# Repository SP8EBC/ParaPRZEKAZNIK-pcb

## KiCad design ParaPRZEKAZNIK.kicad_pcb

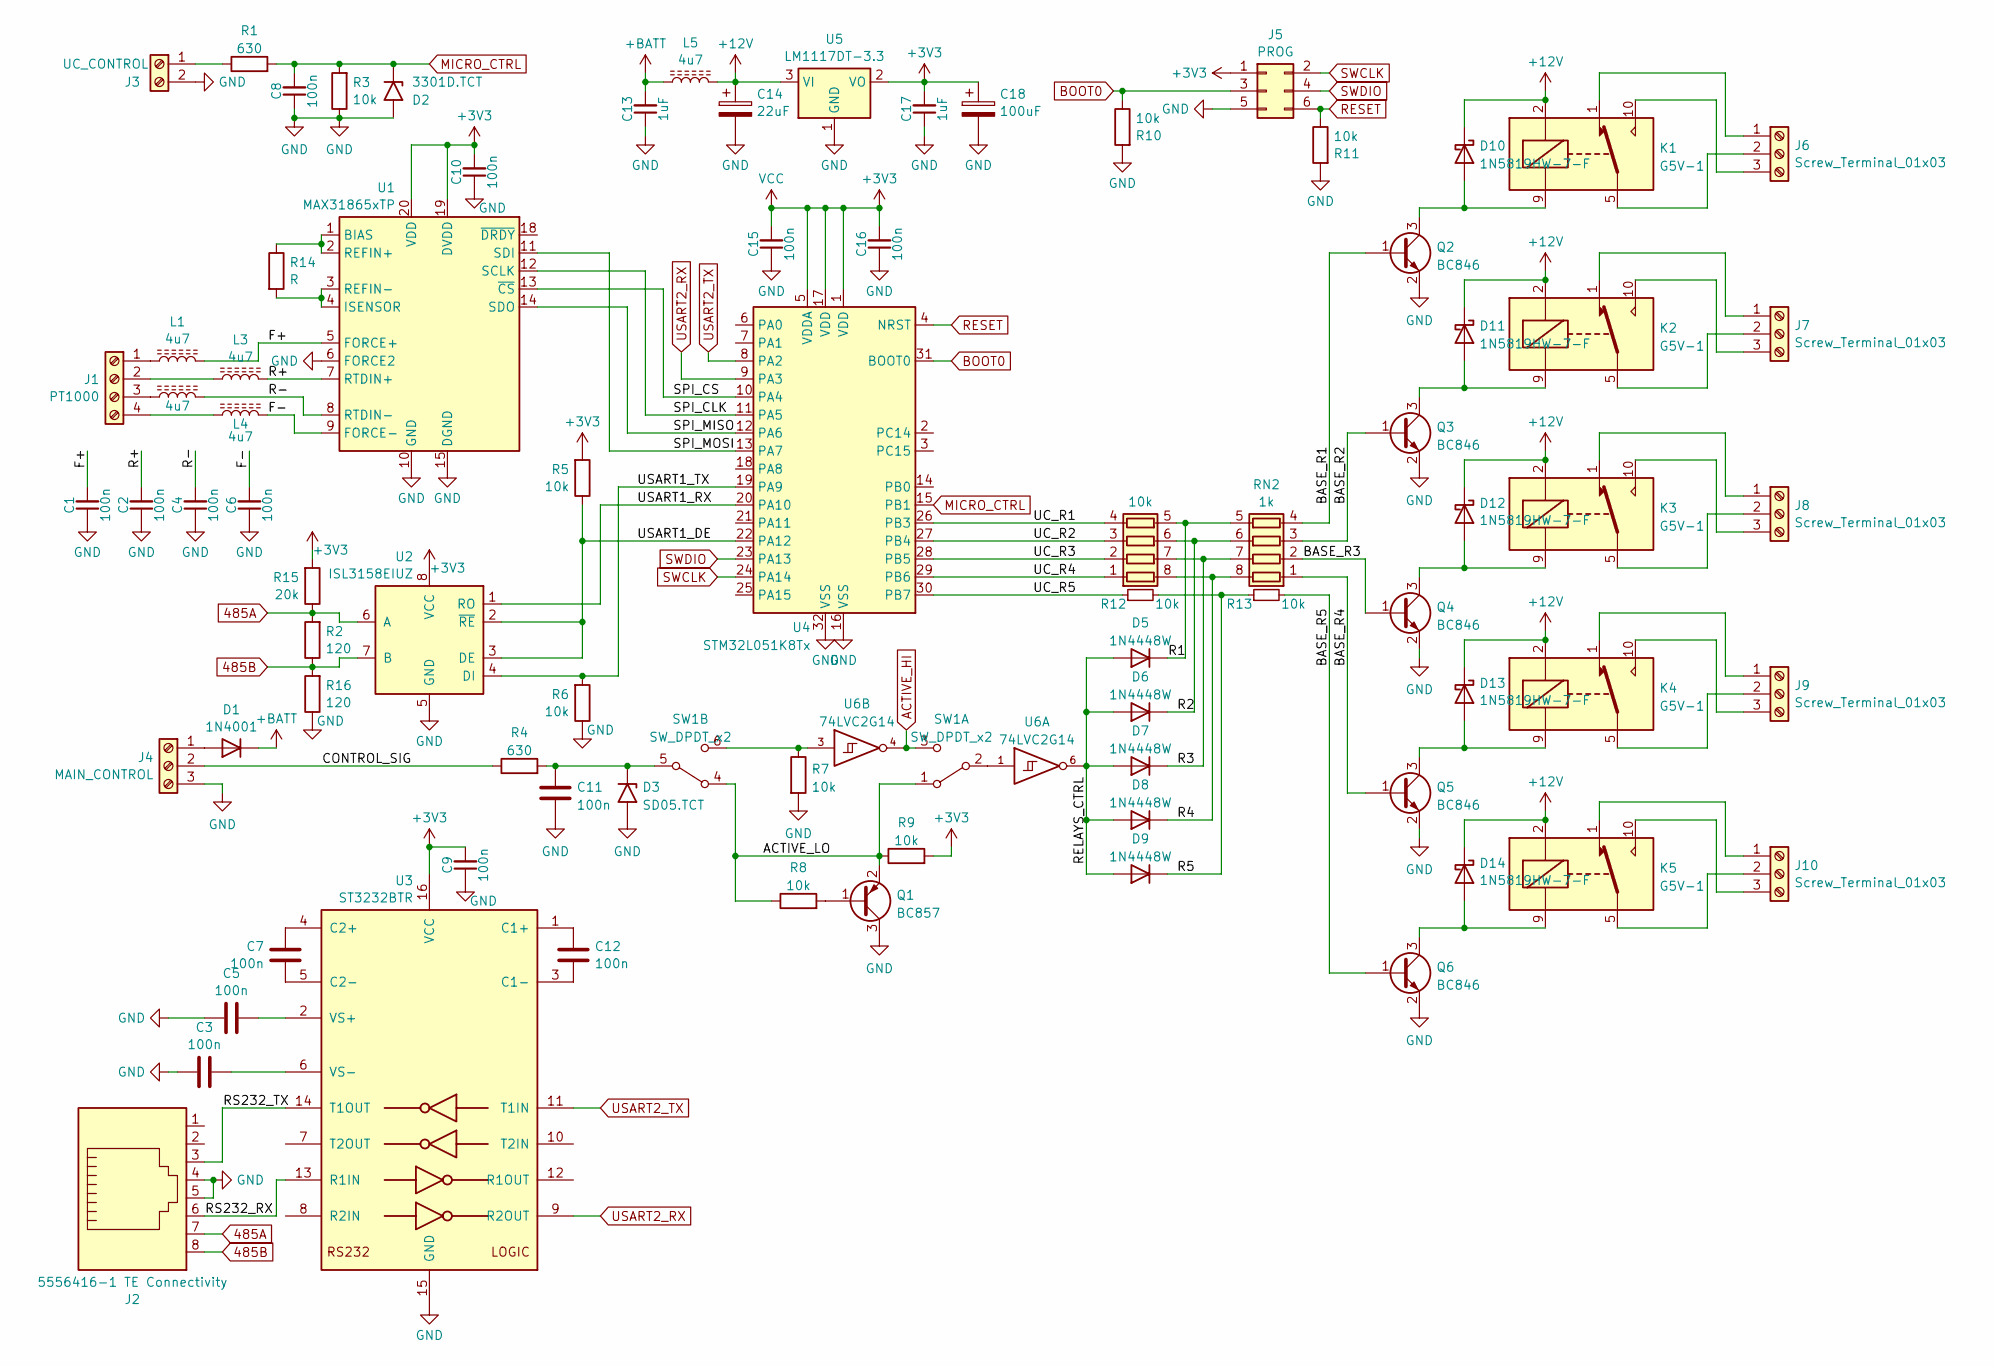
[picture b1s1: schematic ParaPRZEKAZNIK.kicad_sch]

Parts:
C1, C2, C3, C4, C5, C6, C7, C8, C9, C10, C11, C12, C15, C16: 100n; C_0805_2012Metric_Pad1.18x1.45mm_HandSolder
C13, C17: 1uF; C_0805_2012Metric_Pad1.18x1.45mm_HandSolder
C14: 22uF; CP_Radial_D8.0mm_P5.00mm
C18: 100uF; CP_EIA-3528-21_Kemet-B_Pad1.50x2.35mm_HandSolder
D1: 1N4001; D_SMB
D2: 3301D.TCT; D_SOD-323_HandSoldering
D3: SD05.TCT; D_SOD-323_HandSoldering
D5, D6, D7, D8, D9: 1N4448W; D_SOD-123
D10, D11, D12, D13, D14: 1N5819HW-7-F; D_SOD-123
J1: PT1000; PhoenixContact_MCV_1,5_4-G-3.81_1x04_P3.81mm_Vertical
J2: 5556416-1 TE Connectivity; RJ45_OST_PJ012-8P8CX_Vertical
J3: UC_CONTROL; PhoenixContact_MCV_1,5_2-G-3.5_1x02_P3.50mm_Vertical
J4: MAIN_CONTROL; PhoenixContact_MCV_1,5_3-G-3.5_1x03_P3.50mm_Vertical
J5: PROG; PinHeader_2x03_P2.54mm_Vertical
J6, J7, J8, J9, J10: Screw_Terminal_01x03; PhoenixContact_MCV_1,5_3-G-3.5_1x03_P3.50mm_Vertical
K1, K2, K3, K4, K5: G5V-1; Relay_SPDT_Omron_G5V-1
L1, L2, L3, L4, L5: 4u7; L_0805_2012Metric_Pad1.15x1.40mm_HandSolder
Q1: BC857; SOT-23
Q2, Q3, Q4, Q5, Q6: BC846; SOT-23
R1, R4: 630; R_0805_2012Metric_Pad1.20x1.40mm_HandSolder
R2, R16: 120; R_0805_2012Metric_Pad1.20x1.40mm_HandSolder
R3, R5, R6, R7, R8, R9, R10, R11, R12, R13: 10k; R_0805_2012Metric_Pad1.20x1.40mm_HandSolder
R14: R; R_0805_2012Metric_Pad1.20x1.40mm_HandSolder
R15: 20k; R_0805_2012Metric_Pad1.20x1.40mm_HandSolder
RN1: 10k; R_Array_Convex_4x1206
RN2: 1k; R_Array_Convex_4x1206
SW1: SW_DPDT_x2; Alps_SSSS222700
U1: MAX31865xTP; TQFN-20-1EP_5x5mm_P0.65mm_EP3.25x3.25mm
U2: ISL3158EIUZ; MSOP-8_3x3mm_P0.65mm
U3: ST3232BTR; TSSOP-16_4.4x5mm_P0.65mm
U4: STM32L051K8Tx; LQFP-32_7x7mm_P0.8mm
U5: LM1117DT-3.3; TO-252-3_TabPin2
U6: 74LVC2G14; TSOP-6_1.65x3.05mm_P0.95mm

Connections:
485A: J2.7, R2.2, R15.1, U2.6 (A)
485B: J2.8, R2.1, R16.2, U2.7 (B)
+3V3: C9.2, C10.2, C15.2, C16.2, C17.2, C18.1, J5.1, R5.2, R9.2, R15.2, U1.19 (DVDD), U1.20 (VDD), U2.8 (VCC), U3.16 (VCC), U4.1 (VDD), U4.5 (VDDA), U4.17 (VDD), U5.2 (VO), U6.5 (VCC)
+12V: C14.1, D10.1 (K), D11.1 (K), D12.1 (K), D13.1 (K), D14.1 (K), K1.2, K2.2, K3.2, K4.2, K5.2, L5.2, U5.3 (VI)
+BATT: C13.2, D1.1 (K), L5.1
/ACTIVE_LO: Q1.2 (E), R8.1, R9.1, SW1.1 (A), SW1.4 (A)
/BASE_R1: Q2.1 (B), RN2.4 (R4.1)
/BASE_R2: Q3.1 (B), RN2.3 (R3.1)
/BASE_R3: Q4.1 (B), RN2.2 (R2.1)
/BASE_R4: Q5.1 (B), RN2.1 (R1.1)
/BASE_R5: Q6.1 (B), R13.2
/CONTROL_SIG: J4.2, R4.1
/F+: C1.2, L1.2, U1.5 (FORCE+)
/F-: C6.2, L4.2, U1.9 (FORCE-)
/R1: D5.1 (K), RN1.5 (R4.2), RN2.5 (R4.2)
/R2: D6.1 (K), RN1.6 (R3.2), RN2.6 (R3.2)
/R3: D7.1 (K), RN1.7 (R2.2), RN2.7 (R2.2)
/R4: D8.1 (K), RN1.8 (R1.2), RN2.8 (R1.2)
/R5: D9.1 (K), R12.2, R13.1
/R+: C2.2, L3.2, U1.7 (RTDIN+)
/R-: C4.2, L2.2, U1.8 (RTDIN-)
/RELAYS_CTRL: D5.2 (A), D6.2 (A), D7.2 (A), D8.2 (A), D9.2 (A), U6.6
/RS232_RX: J2.6, U3.13 (R1IN)
/RS232_TX: J2.3, U3.14 (T1OUT)
/SPI_CLK: U1.12 (SCLK), U4.11 (PA5)
/SPI_CS: U1.13 (~CS), U4.10 (PA4)
/SPI_MISO: U1.14 (SDO), U4.12 (PA6)
/SPI_MOSI: U1.11 (SDI), U4.13 (PA7)
/UC_R1: RN1.4 (R4.1), U4.26 (PB3)
/UC_R2: RN1.3 (R3.1), U4.27 (PB4)
/UC_R3: RN1.2 (R2.1), U4.28 (PB5)
/UC_R4: RN1.1 (R1.1), U4.29 (PB6)
/UC_R5: R12.1, U4.30 (PB7)
/USART1_DE: R5.1, U2.2 (~RE), U2.3 (DE), U4.22 (PA12)
/USART1_RX: U2.1 (RO), U4.20 (PA10)
/USART1_TX: R6.2, U2.4 (DI), U4.19 (PA9)
ACTIVE_HI: SW1.3 (C), U6.4
BOOT0: J5.3, R10.1, U4.31 (BOOT0)
GND: C1.1, C2.1, C3.2, C4.1, C5.2, C6.1, C8.1, C9.1, C10.1, C11.2, C13.1, C14.2, C15.1, C16.1, C17.1, C18.2, D2.2 (A2), D3.2 (A2), J2.4, J2.5, J3.2, J4.3, J5.5, Q1.3 (C), Q2.2 (E), Q3.2 (E), Q4.2 (E), Q5.2 (E), Q6.2 (E), R3.1, R6.1, R7.2, R10.2, R11.2, R16.1, U1.6 (FORCE2), U1.10 (GND), U1.15 (DGND), U1.16 (GND), U1.21 (GND), U2.5 (GND), U3.15 (GND), U4.16 (VSS), U4.32 (VSS), U5.1 (GND), U6.2 (GND)
MICRO_CTRL: C8.2, D2.1 (A1), R1.2, R3.2, U4.15 (PB1)
unnamed: D1.2 (A), J4.1
unnamed: C11.1, D3.1 (A1), R4.2, SW1.5 (B)
unnamed: D10.2 (A), K1.9, Q2.3 (C)
unnamed: D11.2 (A), K2.9, Q3.3 (C)
unnamed: D12.2 (A), K3.9, Q4.3 (C)
unnamed: D13.2 (A), K4.9, Q5.3 (C)
unnamed: D14.2 (A), K5.9, Q6.3 (C)
unnamed: J1.1, L1.1
unnamed: J1.2, L3.1
unnamed: J1.3, L2.1
unnamed: J1.4, L4.1
unnamed: J3.1, R1.1
unnamed: J6.1, K1.1
unnamed: J6.2, K1.5, K1.6
unnamed: J6.3, K1.10
unnamed: J7.1, K2.1
unnamed: J7.2, K2.5, K2.6
unnamed: J7.3, K2.10
unnamed: J8.1, K3.1
unnamed: J8.2, K3.5, K3.6
unnamed: J8.3, K3.10
unnamed: J9.1, K4.1
unnamed: J9.2, K4.5, K4.6
unnamed: J9.3, K4.10
unnamed: J10.1, K5.1
unnamed: J10.2, K5.5, K5.6
unnamed: J10.3, K5.10
unnamed: Q1.1 (B), R8.2
unnamed: SW1.2 (B), U6.1
unnamed: R7.1, SW1.6 (C), U6.3
unnamed: R14.1, U1.1 (BIAS), U1.2 (REFIN+)
unnamed: R14.2, U1.3 (REFIN-), U1.4 (ISENSOR)
unnamed: C12.1, U3.1 (C1+)
unnamed: C12.2, U3.3 (C1-)
unnamed: C7.1, U3.4 (C2+)
unnamed: C7.2, U3.5 (C2-)
unnamed: C5.1, U3.2 (VS+)
unnamed: C3.1, U3.6 (VS-)
RESET: J5.6, R11.1, U4.4 (NRST)
SWCLK: J5.2, U4.24 (PA14)
SWDIO: J5.4, U4.23 (PA13)
USART2_RX: U3.9 (R2OUT), U4.9 (PA3)
USART2_TX: U3.11 (T1IN), U4.8 (PA2)

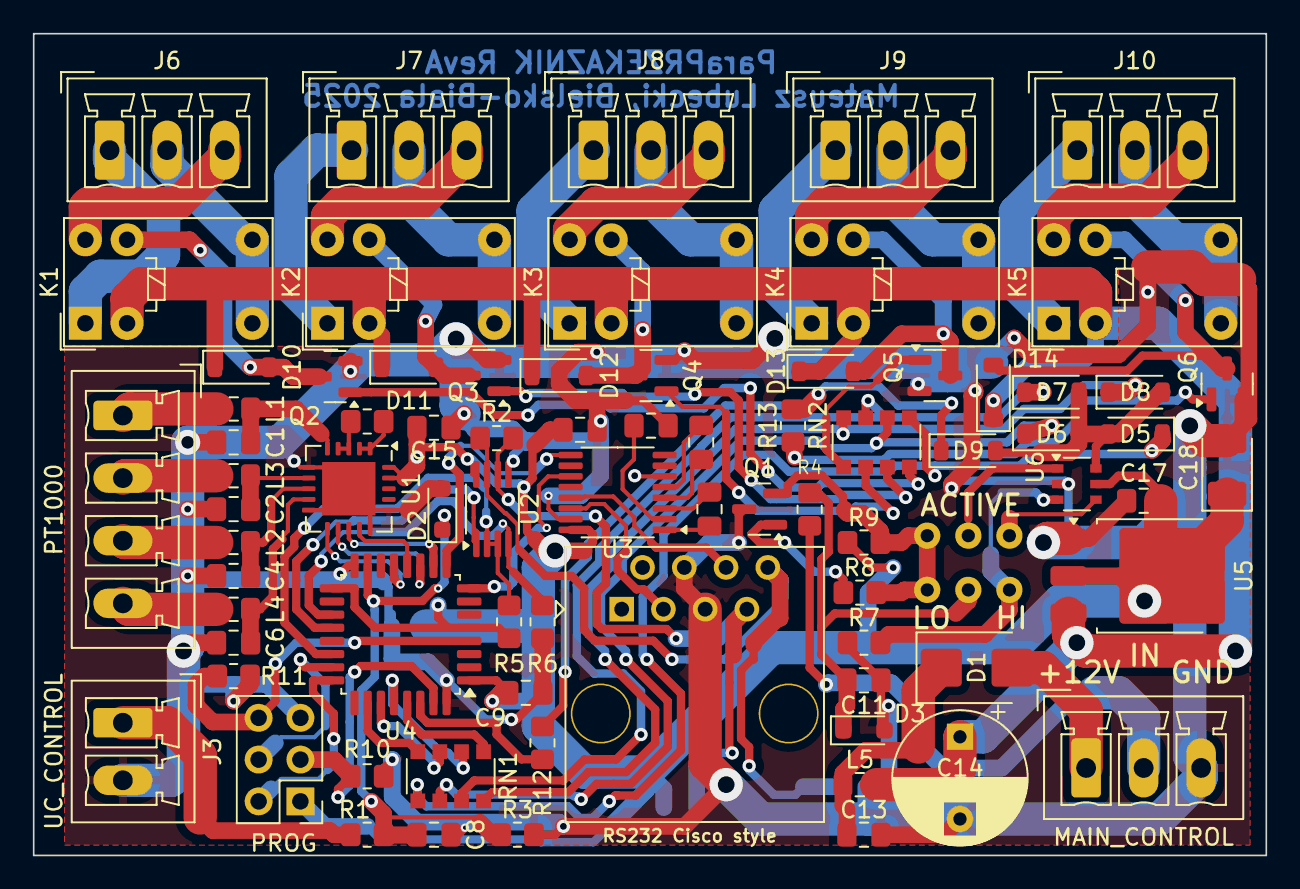
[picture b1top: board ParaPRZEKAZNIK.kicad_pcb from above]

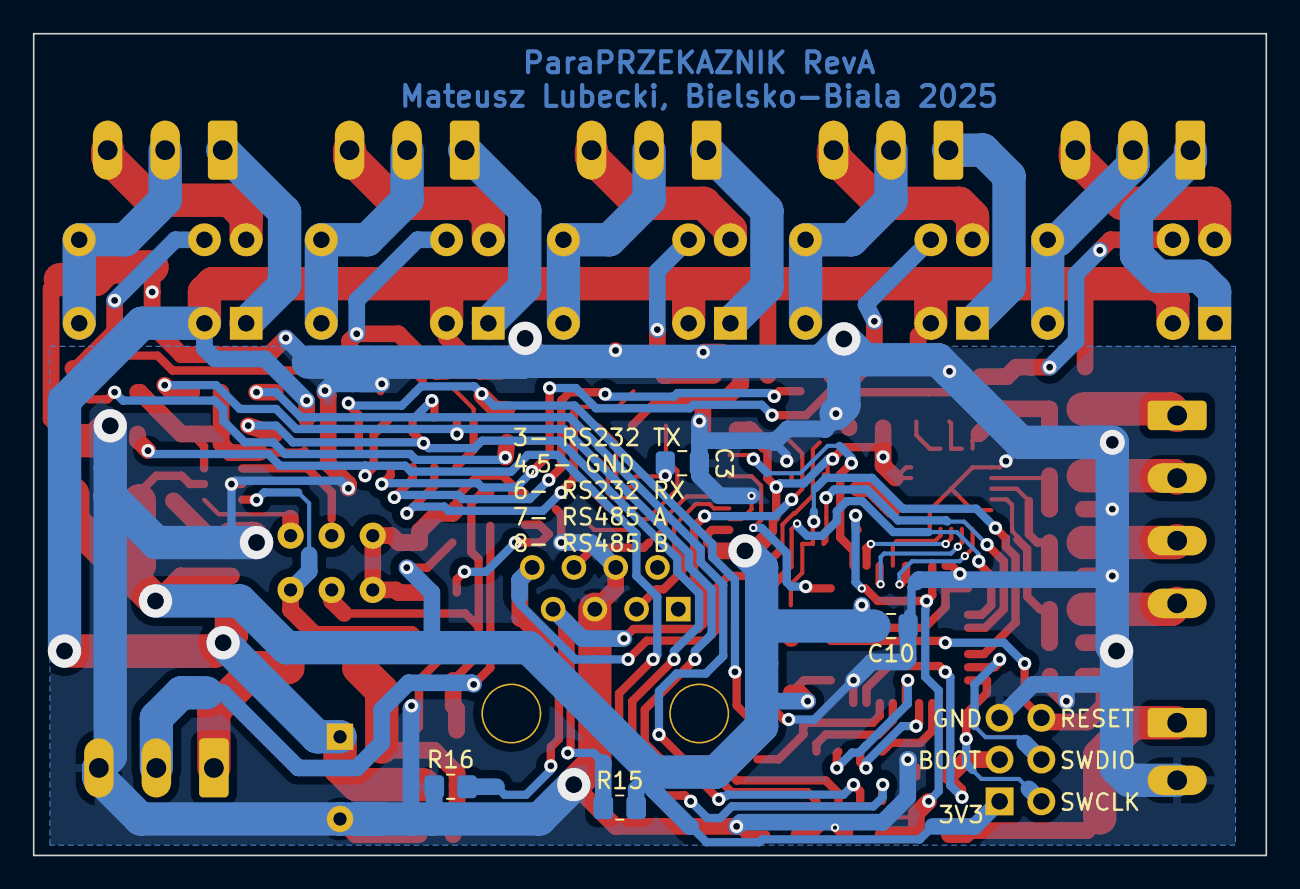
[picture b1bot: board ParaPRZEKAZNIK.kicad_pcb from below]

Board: 2 copper layers, 75.0 x 50.0 mm, 82 parts (4 on the bottom side), 83 nets.

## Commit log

2025-07-03 gitignore
2025-07-03 kicad_files
2025-07-07 schematic
2025-07-08 componets placed on pcb
2025-07-09 partially routed
2025-07-11 done and exported
